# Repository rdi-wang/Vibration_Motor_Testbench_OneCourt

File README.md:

A small testbench PCB designed to test a DRV2603RUNT vibration motor controller 

Board inputs: 
- Enable
- PWM -> motor vibration frequency
- LRA/ERM -> vibration motor mode, LRA - linear motion, ERM - rotational motion
- VDD

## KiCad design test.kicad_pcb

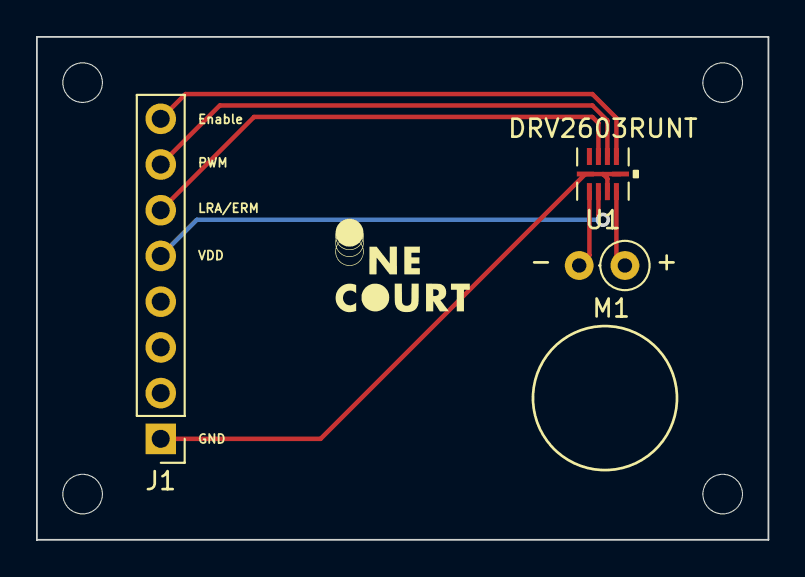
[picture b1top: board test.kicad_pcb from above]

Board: 2 copper layers, 40.6 x 27.9 mm, 3 parts (0 on the bottom side), 7 nets.

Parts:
J1: Conn_01x08_MountingPin; PinHeader_1x08_P2.54mm_Vertical
M1 : VG0832012 LRA; R_Axial_DIN0207_L6.3mm_D2.5mm_P2.54mm_Vertical
U1: DRV2603RUNT

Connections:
GND: J1.1, U1.5 (GND), U1.8 (GND), U1.10 (GND)
unnamed: J1.5, U1.7 (VDD)
unnamed: J1.6, U1.3 (LRA/*ERM)
unnamed: J1.7, U1.2 (PWM)
unnamed: J1.8, U1.1 (EN)
unnamed: M1.1, U1.9 (OUT+)
unnamed: M1.2, U1.6 (OUT-)

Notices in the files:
parts and their libraries:
Copyright 2021 Accelerated Designs. All rights reserved.
